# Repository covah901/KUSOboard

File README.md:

# KUSOboard
KUSOboard is a Longan Nano based keyboard using KarlK90's branch of QMK 
All info on Karl's branch and YAEMK can be found here: https://karlk90.github.io/yaemk-split-kb/

Regarding the naming of the files, I had started out meaning to make an Atreus size board, but decided against it shortly after starting the project. 
It was reduced to something more like a Reviung39. 

album: https://imgur.com/a/PWmJwKW

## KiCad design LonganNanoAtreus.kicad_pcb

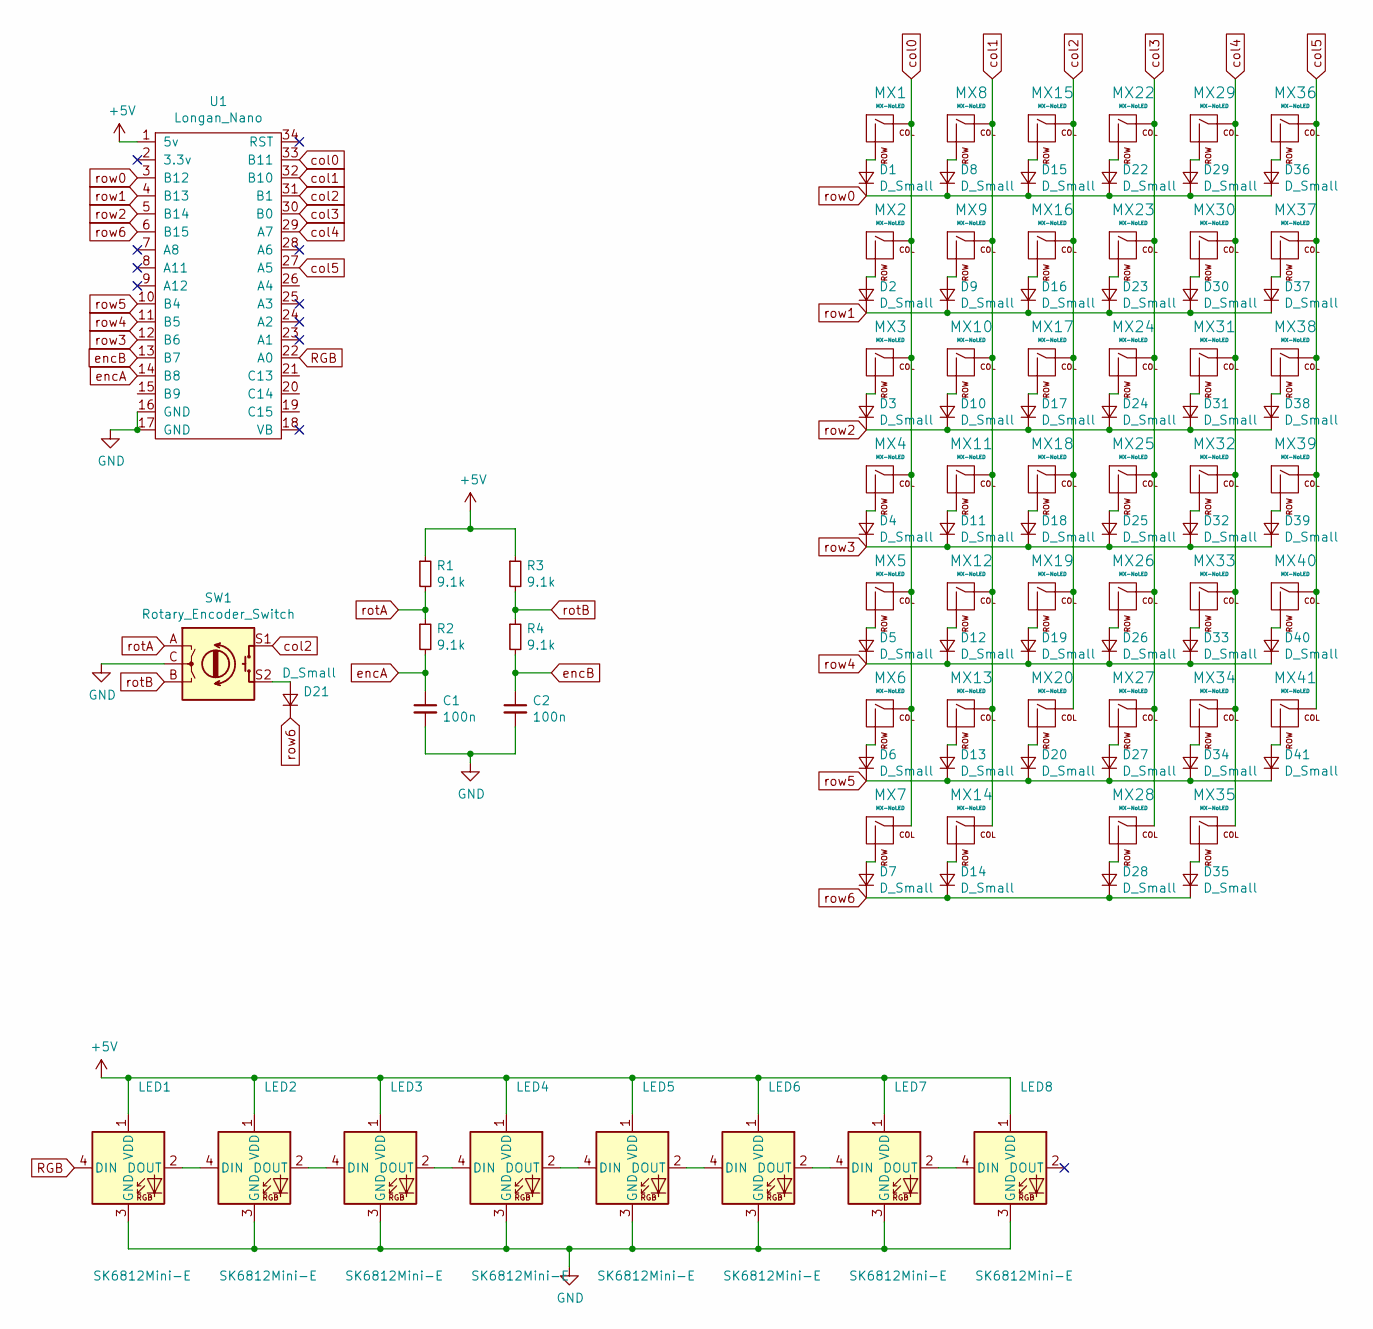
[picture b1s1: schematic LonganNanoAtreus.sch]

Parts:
C1, C2: 100n; C_0805_2012Metric_Pad1.15x1.40mm_HandSolder
D1, D2, D3, D4, D5, D6, D7, D8, D9, D10, D11, D12, D13, D14, D15, D16, D17, D18, D19, D20, D21, D22, D23, D24, D25, D26, D27, D28, D29, D30, D31, D32, D33, D34, D35, D36, D37, D38, D39, D40, D41: D_Small; D_SOD-123F
LED1, LED2, LED3, LED4, LED5, LED6, LED7, LED8: SK6812Mini-E; SK6812-MINI-E
MX1, MX2, MX3, MX4, MX5, MX6, MX7, MX8, MX9, MX10, MX11, MX12, MX13, MX14, MX15, MX16, MX17, MX18, MX19, MX20, MX22, MX23, MX24, MX25, MX26, MX27, MX28, MX29, MX30, MX31, MX32, MX33, MX34, MX35, MX36, MX37, MX38, MX39, MX40, MX41: MX-NoLED; MXOnly-1U-NoLED
R1, R2, R3, R4: 9.1k; R_0805_2012Metric_Pad1.15x1.40mm_HandSolder
SW1: Rotary_Encoder_Switch; EVQWGD001
U1: Longan_Nano

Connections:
+5V: LED1.1 (VDD), LED2.1 (VDD), LED3.1 (VDD), LED4.1 (VDD), LED5.1 (VDD), LED6.1 (VDD), LED7.1 (VDD), LED8.1 (VDD), R1.1, R3.1, U1.1 (5v)
GND: C1.2, C2.2, LED1.3 (GND), LED2.3 (GND), LED3.3 (GND), LED4.3 (GND), LED5.3 (GND), LED6.3 (GND), LED7.3 (GND), LED8.3 (GND), SW1.C, U1.16 (GND), U1.17 (GND)
unnamed: D1.2 (A), MX1.2 (ROW)
unnamed: D2.2 (A), MX2.2 (ROW)
unnamed: D3.2 (A), MX3.2 (ROW)
unnamed: D4.2 (A), MX4.2 (ROW)
unnamed: D5.2 (A), MX5.2 (ROW)
unnamed: D6.2 (A), MX6.2 (ROW)
unnamed: D7.2 (A), MX7.2 (ROW)
unnamed: D8.2 (A), MX8.2 (ROW)
unnamed: D9.2 (A), MX9.2 (ROW)
unnamed: D10.2 (A), MX10.2 (ROW)
unnamed: D11.2 (A), MX11.2 (ROW)
unnamed: D12.2 (A), MX12.2 (ROW)
unnamed: D13.2 (A), MX13.2 (ROW)
unnamed: D14.2 (A), MX14.2 (ROW)
unnamed: D15.2 (A), MX15.2 (ROW)
unnamed: D16.2 (A), MX16.2 (ROW)
unnamed: D17.2 (A), MX17.2 (ROW)
unnamed: D18.2 (A), MX18.2 (ROW)
unnamed: D19.2 (A), MX19.2 (ROW)
unnamed: D20.2 (A), MX20.2 (ROW)
unnamed: D21.2 (A), SW1.S2
unnamed: D22.2 (A), MX22.2 (ROW)
unnamed: D23.2 (A), MX23.2 (ROW)
unnamed: D24.2 (A), MX24.2 (ROW)
unnamed: D25.2 (A), MX25.2 (ROW)
unnamed: D26.2 (A), MX26.2 (ROW)
unnamed: D27.2 (A), MX27.2 (ROW)
unnamed: D28.2 (A), MX28.2 (ROW)
unnamed: D29.2 (A), MX29.2 (ROW)
unnamed: D30.2 (A), MX30.2 (ROW)
unnamed: D31.2 (A), MX31.2 (ROW)
unnamed: D32.2 (A), MX32.2 (ROW)
unnamed: D33.2 (A), MX33.2 (ROW)
unnamed: D34.2 (A), MX34.2 (ROW)
unnamed: D35.2 (A), MX35.2 (ROW)
unnamed: D36.2 (A), MX36.2 (ROW)
unnamed: D37.2 (A), MX37.2 (ROW)
unnamed: D38.2 (A), MX38.2 (ROW)
unnamed: D39.2 (A), MX39.2 (ROW)
unnamed: D40.2 (A), MX40.2 (ROW)
unnamed: D41.2 (A), MX41.2 (ROW)
unnamed: LED1.2 (DOUT), LED2.4 (DIN)
unnamed: LED2.2 (DOUT), LED3.4 (DIN)
unnamed: LED3.2 (DOUT), LED4.4 (DIN)
unnamed: LED4.2 (DOUT), LED5.4 (DIN)
unnamed: LED5.2 (DOUT), LED6.4 (DIN)
unnamed: LED6.2 (DOUT), LED7.4 (DIN)
unnamed: LED7.2 (DOUT), LED8.4 (DIN)
RGB: LED1.4 (DIN), U1.22 (A0)
col0: MX1.1 (COL), MX2.1 (COL), MX3.1 (COL), MX4.1 (COL), MX5.1 (COL), MX6.1 (COL), MX7.1 (COL), U1.33 (B11)
col1: MX8.1 (COL), MX9.1 (COL), MX10.1 (COL), MX11.1 (COL), MX12.1 (COL), MX13.1 (COL), MX14.1 (COL), U1.32 (B10)
col2: MX15.1 (COL), MX16.1 (COL), MX17.1 (COL), MX18.1 (COL), MX19.1 (COL), MX20.1 (COL), SW1.S1, U1.31 (B1)
col3: MX22.1 (COL), MX23.1 (COL), MX24.1 (COL), MX25.1 (COL), MX26.1 (COL), MX27.1 (COL), MX28.1 (COL), U1.30 (B0)
col4: MX29.1 (COL), MX30.1 (COL), MX31.1 (COL), MX32.1 (COL), MX33.1 (COL), MX34.1 (COL), MX35.1 (COL), U1.29 (A7)
col5: MX36.1 (COL), MX37.1 (COL), MX38.1 (COL), MX39.1 (COL), MX40.1 (COL), MX41.1 (COL), U1.27 (A5)
encA: C1.1, R2.2, U1.14 (B8)
encB: C2.1, R4.2, U1.13 (B7)
rotA: R1.2, R2.1, SW1.A
rotB: R3.2, R4.1, SW1.B
row0: D1.1 (K), D8.1 (K), D15.1 (K), D22.1 (K), D29.1 (K), D36.1 (K), U1.3 (B12)
row1: D2.1 (K), D9.1 (K), D16.1 (K), D23.1 (K), D30.1 (K), D37.1 (K), U1.4 (B13)
row2: D3.1 (K), D10.1 (K), D17.1 (K), D24.1 (K), D31.1 (K), D38.1 (K), U1.5 (B14)
row3: D4.1 (K), D11.1 (K), D18.1 (K), D25.1 (K), D32.1 (K), D39.1 (K), U1.12 (B6)
row4: D5.1 (K), D12.1 (K), D19.1 (K), D26.1 (K), D33.1 (K), D40.1 (K), U1.11 (B5)
row5: D6.1 (K), D13.1 (K), D20.1 (K), D27.1 (K), D34.1 (K), D41.1 (K), U1.10 (B4)
row6: D7.1 (K), D14.1 (K), D21.1 (K), D28.1 (K), D35.1 (K), U1.6 (B15)

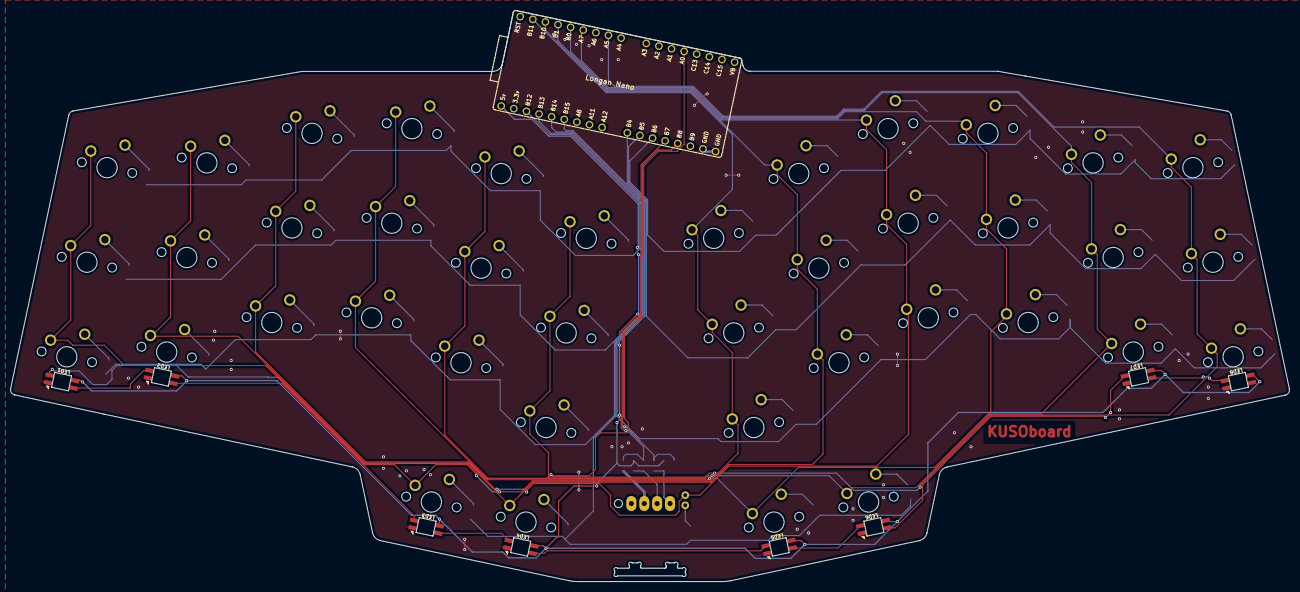
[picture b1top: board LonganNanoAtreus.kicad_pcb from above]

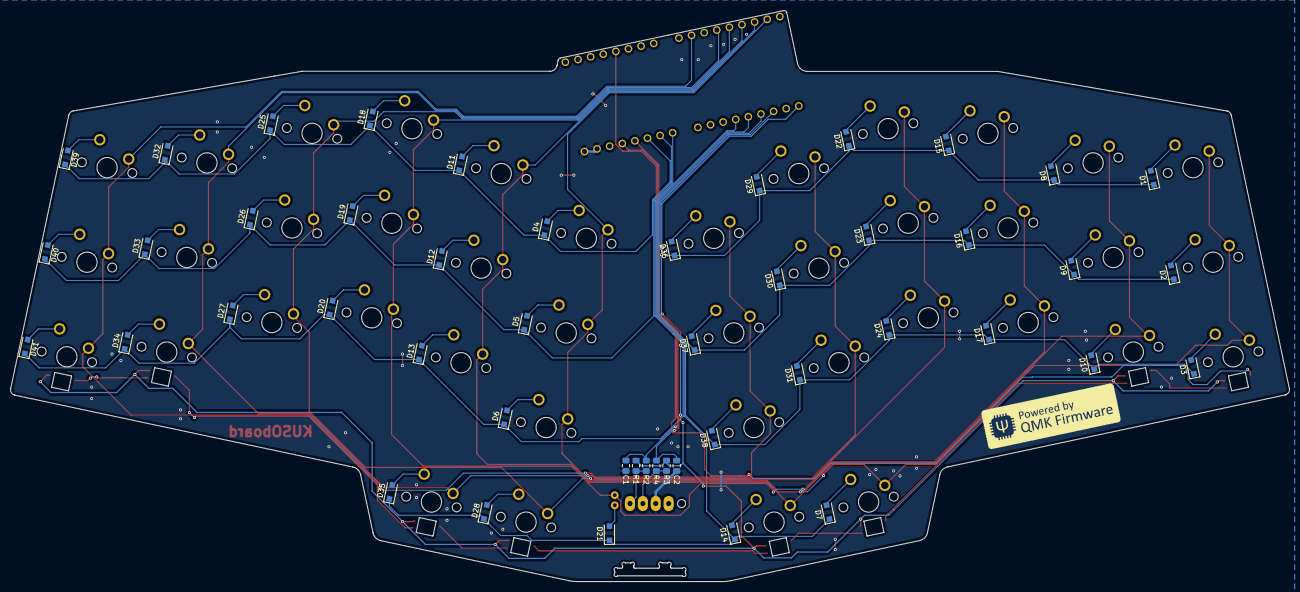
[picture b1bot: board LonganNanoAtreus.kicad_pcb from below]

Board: 2 copper layers, 252.0 x 112.5 mm, 97 parts (47 on the bottom side), 68 nets.

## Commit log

2021-06-12 Create LonganNanoAtreus
2021-06-12 Create LICENSE
2021-07-02 updated encoder to bool
